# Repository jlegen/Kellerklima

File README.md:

# Kellerklima
## Arduino-based humidity controller with indoor and outdoor sensors for fan control

I made this device to dry my (and others :) cellars by mostly making use of the times when the *absolute* humidity outdoors is lower than indoors. 
For this, two sensors are used to measure humidity and temperature, indoors and outdoors.
Though this seems to be quite a common design, i only found some rather costly commercial products. This one mostly uses cheap and popular modules.

## Basic principle
Temperature and humidity values from inside and outside are used to calculate the absolute humidity. If the outside is less humid than the inside, the fan is started (or, alternatively, the window is opened, if an opener is used instead of a fan).
There's a maximum fan runtime to be configured. After this time, either the fan is paused, or - using the 2nd relay - a dehumidifier unit can be started for a set period of time.
This repeats until the target humidity value for the inside is reached, or one of the user-defined criterias change:
* fan and dehumidifier only run if the inside humidity is above the trigger value
* fan only runs if inside temperature is above a minimum value
* fan only runs if outside temperature is above a minimum value
* fan and dehumidifier only run if the runtime limit per day (24h) is not reached yet

Defaults are: 
* dew point difference between indoors and outdoors >= 3: switch fan on
* dew point difference between indoors and outdoors < 1: switch fan off
* humidity hysteresis for trigger: 1 
	* indoor humiditity >= <trigger value>: switch fan/dehumidifier on
	* indoor humiditity < <trigger value - 1>: switch fan/dehumidifier off

## Implementation

The regulation makes use of configurable hysteresis values for activation and deactivation, to avoid "flapping", and a fan being turned on and off too quickly.
All parameters can be configured using the rotary encoder and a menu system with the 1602 LCD.
Optionally, if an ESP-01 module with ESP-Link (https://github.com/jeelabs/esp-link) is equipped, all parameters can be set using telnet. 
This ESP-01 module also allows to remotely flash the arduino code of the controller, and to monitor all activities of the control box remotely. Parameters can be defined using simple commands, and also fan or dehumidifier can be switched on and off, overriding the regulation.
the libraries used are commented in the code.

Update: It turned out that the DHT22 sensors are cr*p, they "wear out" quite quickly, showing wrong humidity data after a few weeks.
To be able to make use of better quality I2C sensors like BME280 or SHT31, i added an I2C booster/bus driver IC to allow for the long(er) wires i needed. For me, 10m do work just fine with SHT31, there are reports that up to 100m are possible, too.
Additionally, i did not manage to get the SLIP protocol running reliably using the ESP-Link, but i still regard the ESP-01 as useful, since the arduino not only can be flashed "OTA" using ESP-link, the new version also allows to monitor the arduino's activities using EPS-link's "µC Console", and the whole thing can be controlled remotely using a set of commands to set temperatures and other parameters. 
Next hardware revision should probably use an ESP module as controller... 

Update 2: Meanwhile, the system is running for more than a year in "production". Works like a charm... :-)

# Gallery

box in normal run mode; the LCD is switched off after a few minutes of inactivity

rotary encoder at the right - is used to scroll through values, testing the relay, and to set most parameters

PCB version finally ready (V1.2)

new PCB for sensors - tailored to fit into cheap waterproof boxes (65X58X35mm)

like these

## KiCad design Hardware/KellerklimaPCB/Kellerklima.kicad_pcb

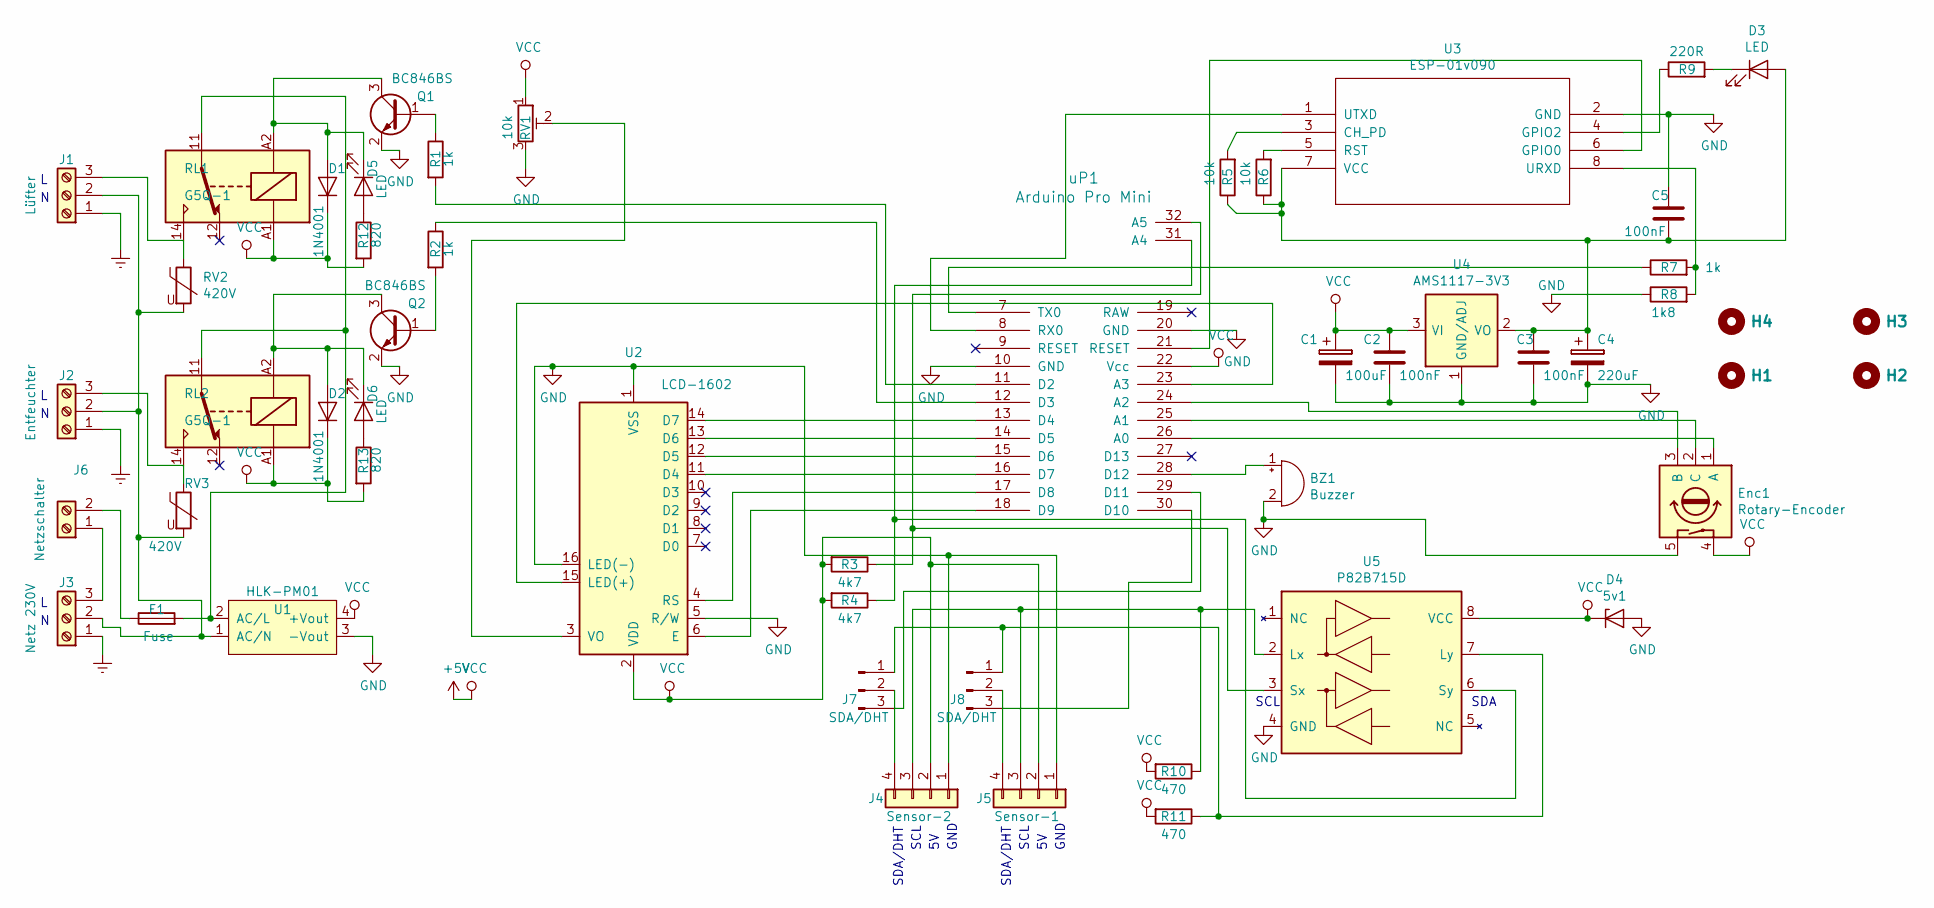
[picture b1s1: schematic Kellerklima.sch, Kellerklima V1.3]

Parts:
BZ1: Buzzer
C1: 100uF
C2, C3, C5: 100nF
C4: 220uF
D1, D2: 1N4001; D_DO-41_SOD81_P10.16mm_Horizontal
D3, D5, D6: LED
D4: 5v1
Enc1: Rotary-Encoder
F1: Fuse
H1, H2, H3, H4: Hole
J1: Lüfter; TerminalBlock_Phoenix_MKDS1.5-3pol
J2: Entfeuchter; TerminalBlock_Phoenix_MKDS1.5-3pol
J3: Netz 230V; TerminalBlock_Phoenix_MKDS1.5-3pol
J4: Sensor-2
J5: Sensor-1
J6: Netzschalter; TerminalBlock_Phoenix_MKDS1.5-2pol
J7, J8: SDA/DHT
Q1, Q2: BC846BS; SOT-323
R1, R2, R7: 1k
R3, R4: 4k7
R5, R6: 10k
R8: 1k8
R9: 220R
R10, R11: 470
R12, R13: 820
RL1, RL2: G5Q-1; Relay_SPDT_Finder_40.51
RV1: 10k
RV2, RV3: 420V; RV_Disc_D7mm_W3.9mm_P5mm
U1: HLK-PM01; ACDC-Converter_MeanWell-IRM-02-x
U2: LCD-1602; WC1602A
U3: ESP-01v090; PinSocket_2x04_P2.54mm_Vertical
U4: AMS1117-3V3; MPN LM1117
U5: P82B715D
uP1: Arduino Pro Mini

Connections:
+5V: C1.1, C2.1, D1.1 (K), D2.1 (K), D4.1 (K), Enc1.4, J4.2, J5.2, R3.2, R4.2, R10.2, R11.2, R12.2, R13.2, RL1.A1, RL2.A1, RV1.1, U1.4 (+Vout), U2.2 (VDD), U4.3 (VI), U5.8 (VCC), uP1.22 (Vcc)
Earth: J1.1, J2.1, J3.1
GND: BZ1.2 (+), C1.2, C2.2, C3.2, C4.2, C5.1, D4.2 (A), Enc1.5, J4.1, J5.1, Q1.2 (E), Q2.2 (E), R8.1, RV1.3, U1.3 (-Vout), U2.1 (VSS), U2.5 (R/W), U2.16 (LED(-)), U3.2 (GND), U4.1 (GND/ADJ), U5.4 (GND), uP1.10 (GND), uP1.20 (GND)
unnamed: BZ1.1 (-), uP1.28 (D12)
unnamed: C3.1, C4.1, C5.2, D3.2 (A), R5.1, R6.1, U3.7 (VCC), U4.2 (VO)
unnamed: D1.2 (A), D5.1 (K), Q1.3 (C), RL1.A2
unnamed: D2.2 (A), D6.1 (K), Q2.3 (C), RL2.A2
unnamed: D3.1 (K), R9.2
unnamed: D5.2 (A), R12.1
unnamed: D6.2 (A), R13.1
unnamed: Enc1.1 (A), uP1.26 (A0)
unnamed: Enc1.2 (C), uP1.25 (A1)
unnamed: Enc1.3 (B), uP1.24 (A2)
unnamed: F1.1, J6.2
unnamed: F1.2, RL1.11, RL2.11, U1.2 (AC/L)
unnamed: J1.2, J2.2, J3.2, RV2.2, RV3.2, U1.1 (AC/N)
unnamed: J1.3, RL1.14, RV2.1
unnamed: J2.3, RL2.14, RV3.1
unnamed: J3.3, J6.1
unnamed: J4.3, J5.3, R10.1, U5.2 (Lx)
unnamed: J4.4, J7.2
unnamed: J5.4, J8.2
unnamed: J7.1, J8.1, R11.1, U5.7 (Ly)
unnamed: J7.3, uP1.29 (D11)
unnamed: J8.3, uP1.30 (D10)
unnamed: Q1.1 (B), R1.1
unnamed: Q2.1 (B), R2.2
unnamed: R1.2, uP1.11 (D2)
unnamed: R2.1, uP1.12 (D3)
unnamed: R3.1, U5.3 (Sx), uP1.32 (A5)
unnamed: R4.1, U5.6 (Sy), uP1.31 (A4)
unnamed: R5.2, U3.3 (CH_PD)
unnamed: R6.2, U3.5 (RST)
unnamed: R7.1, uP1.7 (TX0)
unnamed: R7.2, R8.2, U3.8 (URXD)
unnamed: R9.1, U3.4 (GPIO2)
unnamed: RV1.2, U2.3 (VO)
unnamed: U2.4 (RS), uP1.17 (D8)
unnamed: U2.6 (E), uP1.18 (D9)
unnamed: U2.11 (D4), uP1.16 (D7)
unnamed: U2.12 (D5), uP1.15 (D6)
unnamed: U2.13 (D6), uP1.14 (D5)
unnamed: U2.14 (D7), uP1.13 (D4)
unnamed: U2.15 (LED(+)), uP1.23 (A3)
unnamed: U3.1 (UTXD), uP1.8 (RX0)
unnamed: U3.6 (GPIO0), uP1.21 (RESET)

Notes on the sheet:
SDA
SCL
SDA/DHT
GND

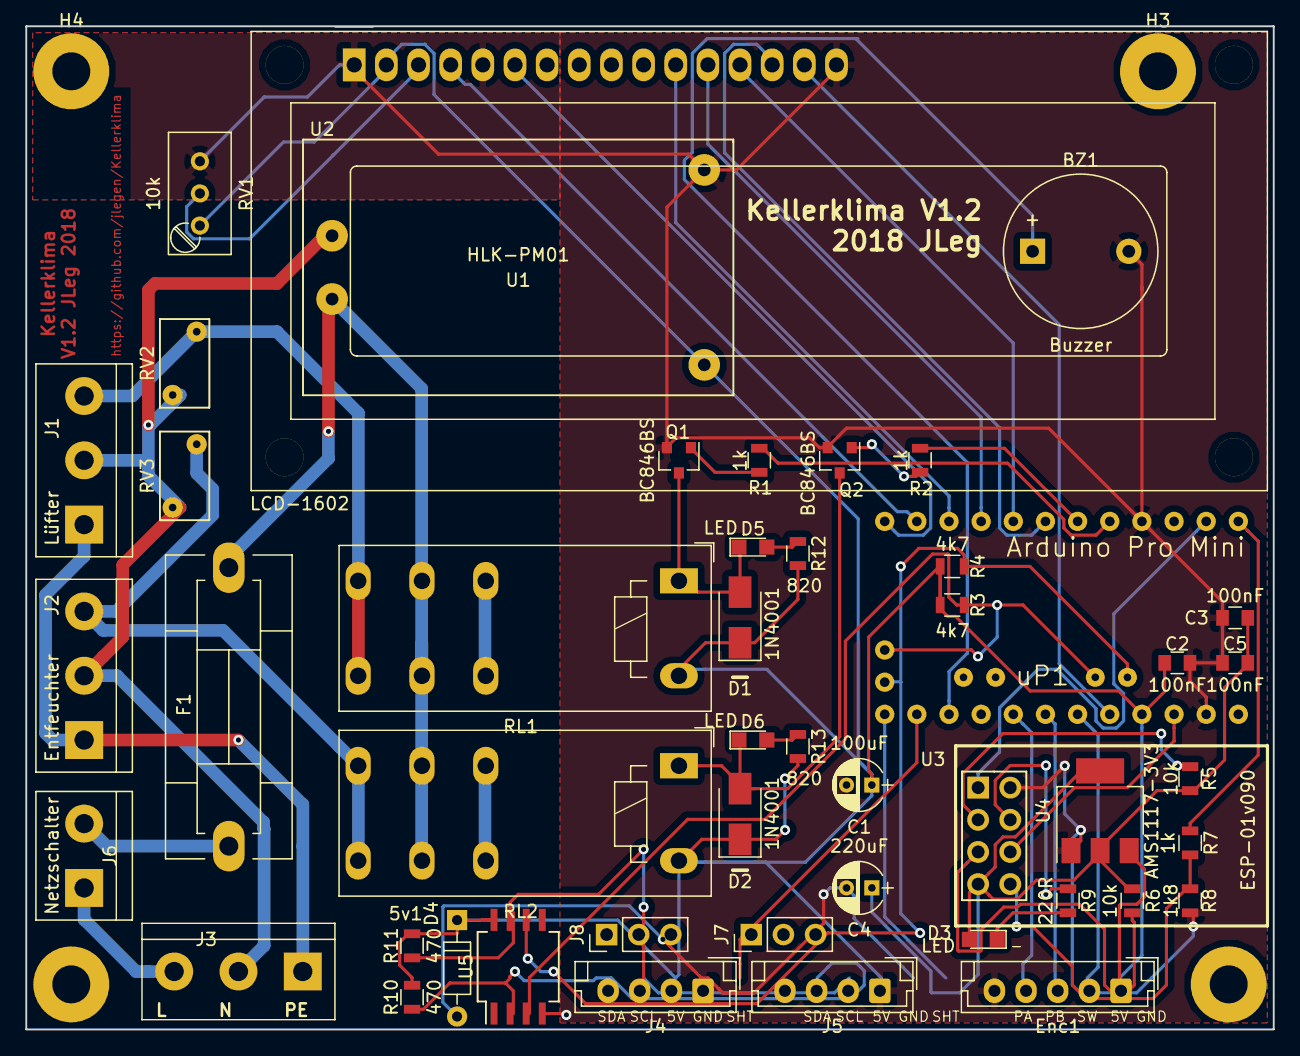
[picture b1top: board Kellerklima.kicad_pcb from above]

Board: 2 copper layers, 98.6 x 79.2 mm, 52 parts (0 on the bottom side), 46 nets.

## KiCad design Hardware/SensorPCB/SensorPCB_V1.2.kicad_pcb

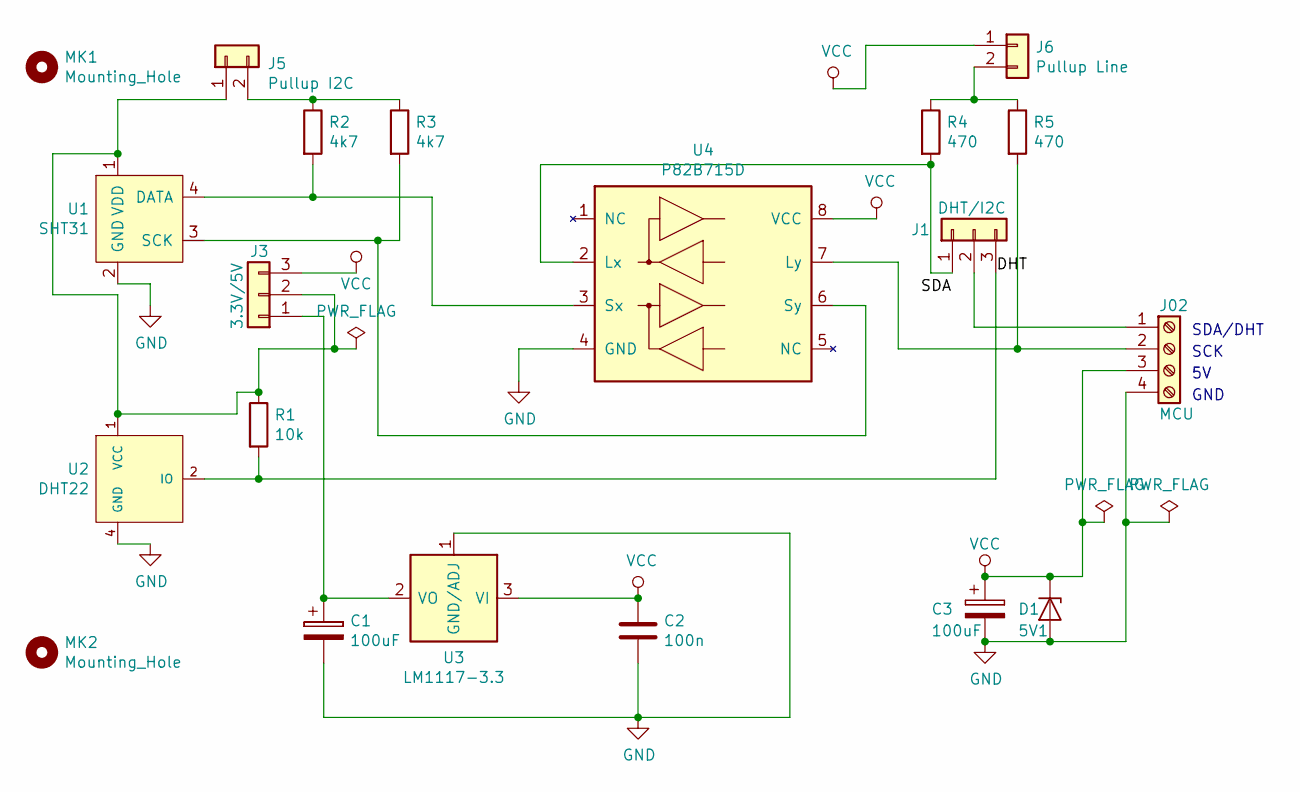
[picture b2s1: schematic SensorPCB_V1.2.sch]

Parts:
C1, C3: 100uF; CP_Radial_D4.0mm_P2.00mm
C2: 100n; C_0805_2012Metric_Pad1.15x1.40mm_HandSolder
D1: 5V1; D_A-405_P7.62mm_Horizontal
J1: DHT/I2C; PinHeader_1x03_P2.54mm_Vertical
J02: MCU; TerminalBlock_bornier-4_P5.08mm
J3: 3.3V/5V; PinHeader_1x03_P2.54mm_Vertical
J5: Pullup I2C; PinHeader_1x02_P2.54mm_Vertical
J6: Pullup Line; PinHeader_1x02_P2.54mm_Vertical
MK1, MK2: Mounting_Hole; MountingHole_2.2mm_M2
R1: 10k; R_0805_2012Metric_Pad1.15x1.40mm_HandSolder
R2, R3: 4k7; R_0805_2012Metric_Pad1.15x1.40mm_HandSolder
R4, R5: 470; R_0805_2012Metric_Pad1.15x1.40mm_HandSolder
U1: SHT31; PinSocket_1x04_P2.54mm_Vertical
U2: DHT22; PinSocket_1x04_P2.54mm_Vertical
U3: LM1117-3.3; SOT-223-3_TabPin2
U4: P82B715D; SO-8_5.3x6.2mm_P1.27mm

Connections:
/DHT: J1.3, R1.2, U2.2 (IO)
GND: C1.2, C2.2, C3.2, D1.2 (A), J02.4, U1.2 (GND), U2.4 (GND), U3.1 (GND/ADJ), U4.4 (GND)
unnamed: C1.1, J3.1, U3.2 (VO)
unnamed: J1.1, R4.2, U4.2 (Lx)
unnamed: J1.2, J02.1
unnamed: J02.2, R5.2, U4.7 (Ly)
unnamed: J3.2, J5.1, R1.1, U1.1 (VDD), U2.1 (VCC)
unnamed: J5.2, R2.1, R3.1
unnamed: J6.2, R4.1, R5.1
unnamed: R2.2, U1.4 (DATA), U4.3 (Sx)
unnamed: R3.2, U1.3 (SCK), U4.6 (Sy)
VCC: C2.1, C3.1, D1.1 (K), J02.3, J3.3, J6.1, U3.3 (VI), U4.8 (VCC)

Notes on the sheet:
SDA/DHT
SCK
GND

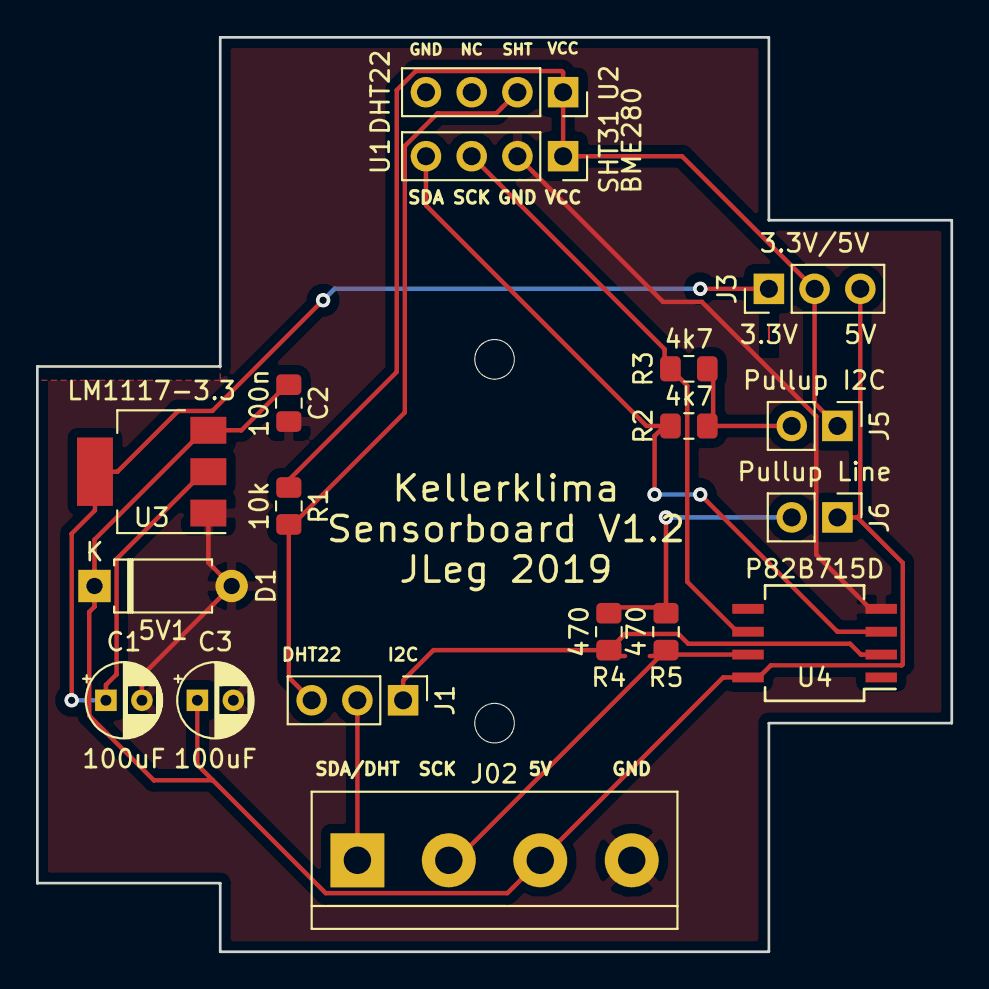
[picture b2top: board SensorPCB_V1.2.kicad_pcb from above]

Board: 2 copper layers, 50.8 x 50.8 mm, 20 parts (0 on the bottom side), 12 nets.

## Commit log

2017-02-06 initial upload
2017-02-27 initial commit
    version modified for enclosure V1
2017-02-27 cleanup
2017-02-27 pics and readme added
2018-02-10 support passive buzzer
    needed 4mm footprint buzzer = passive only
    (pwm version)
2018-02-17 added PCB version
    schematics and gerbers added
2019-02-28 version 1.2
    update for V1.2 stable
2019-02-28 more pics
2019-03-01 added serial error reporting (failing sensors)
2019-09-15 hardware and software fixes
    fixed sensor PCB
    fixed software (hysteresis, operation of dehumidifier)
2019-09-15 added KiCAD project files
    project files for sensor and main PCB added
2019-10-29 new hysteresis and dewpoint handling
    using hysteresis for humidity comparison
    using upper and lower dew point diffs for switching
    better runtime control
    bug fixes
2019-11-02 more fixes
    fixed some visuals
    some cleanup
    more bugs fixed
2019-11-02 code cleanup
    more code cleanup
    integer bug fixed
2019-11-13 some more cleanup
    * removed some obsolete stuff
    * added some more debug msgs for remote sessions
    * fixed wrong dev_stop type
2019-11-13 Update README.md
    adapt to some changes in concept
2019-11-25 bug fixes, temp. calibration
    fixed some lazy type defs
    added new parameters for temperature compensation offsets (LCD and remote)
